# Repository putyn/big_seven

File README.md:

big_seven
=========

3" seven segments wifi clock with a beautiful wooden case

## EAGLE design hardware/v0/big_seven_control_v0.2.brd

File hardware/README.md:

##big_seven hardware

Initital hardware was suppose to have individual current sources for every segement of the display similar to this https://www.dorkbotpdx.org/blog/paul/big_7segment_countdown_timer, until i found the TPIC6x595 which has the same functionality as the 74HC595 (shift register) only higher output voltage.

For the brains the ESP8266 was chosen, simply because its cheap its supporeted by the Arduino IDE and has WiFi. 

##leasens to learn
1. never again use LDO to drop high voltage to low voltage @ high currents https://github.com/esp8266/Arduino/issues/1840

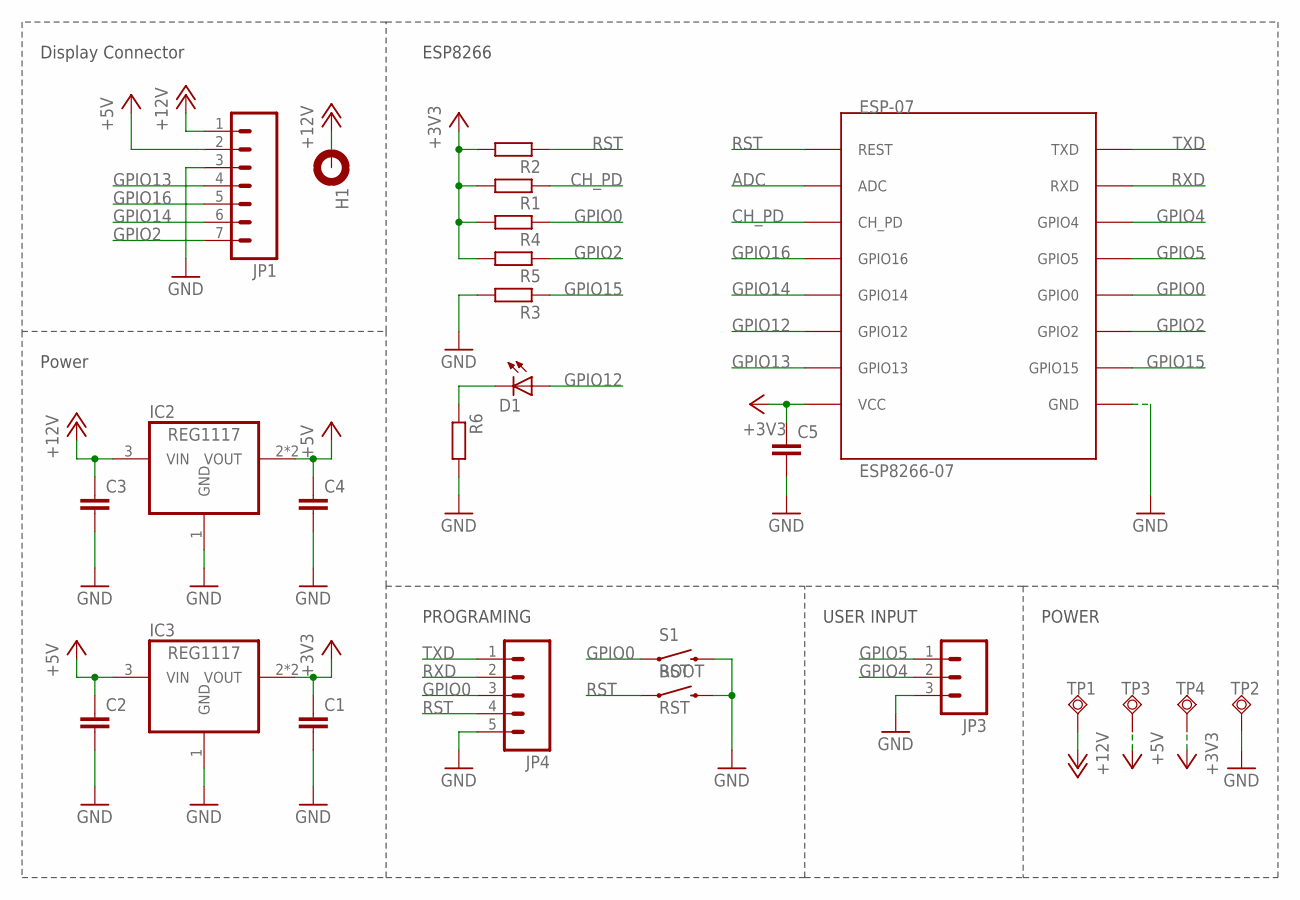
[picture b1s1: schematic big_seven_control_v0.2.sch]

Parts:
C1, C2, C3, C4: C-EUC1206K; C1206K
C5: C-EUC0805; C0805
D1: LEDCHIP-LED0805; CHIP-LED0805
ESP-07: ESP8266-07; ESP-07
H1: MOUNT-PAD-ROUND3.2; 3,2-PAD
IC2, IC3: REG1117; SOT223
JP1: M07LOCK; 1X07_LOCK
JP3: M03LOCK; 1X03_LOCK
JP4: M05LOCK; 1X05_LOCK
R1, R2, R3, R4, R5, R6: R-EU_R0805; R0805
RST: RST; TACTILE-SWITCH-SMD
S1: BOOT; TACTILE-SWITCH-SMD
TP1: 12V; TP20R
TP2: delk; TP20R
TP3: 5V; TP20R
TP4: 3V3; TP20R

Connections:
+3V3: C1.1, C5.1, ESP-07.VCC, IC3.2 (VOUT), IC3.4 (VOUT), R1.2, R2.2, R4.2, R5.2, TP4.TP
+5V: C2.1, C4.1, IC2.2 (VOUT), IC2.4 (VOUT), IC3.3 (VIN), JP1.2, TP3.TP
+12V: C3.1, H1.B3,2, IC2.3 (VIN), JP1.1, TP1.TP
ADC: ESP-07.ADC
CH_PD: ESP-07.CH_PD, R1.1
GND: C1.2, C2.2, C3.2, C4.2, C5.2, ESP-07.GND, IC2.1 (GND), IC3.1 (GND), JP1.3, JP3.3, JP4.5, R3.2, R6.2, RST.3 (2), S1.3 (2), TP2.TP
GPIO0: ESP-07.GPIO0, JP4.3, R4.1, S1.1
GPIO2: ESP-07.GPIO2, JP1.7, R5.1
GPIO4: ESP-07.GPIO4, JP3.2
GPIO5: ESP-07.GPIO5, JP3.1
GPIO12: D1.A, ESP-07.GPIO12
GPIO13: ESP-07.GPIO13, JP1.4
GPIO14: ESP-07.GPIO14, JP1.5
GPIO15: ESP-07.GPIO15, R3.1
GPIO16: ESP-07.GPIO16, JP1.6
unnamed: D1.C, R6.1
RST: ESP-07.REST, JP4.4, R2.1, RST.1
RXD: ESP-07.RXD, JP4.2
TXD: ESP-07.TXD, JP4.1

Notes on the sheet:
Display Connector
Power
ESP8266
PROGRAMING
USER INPUT
POWER

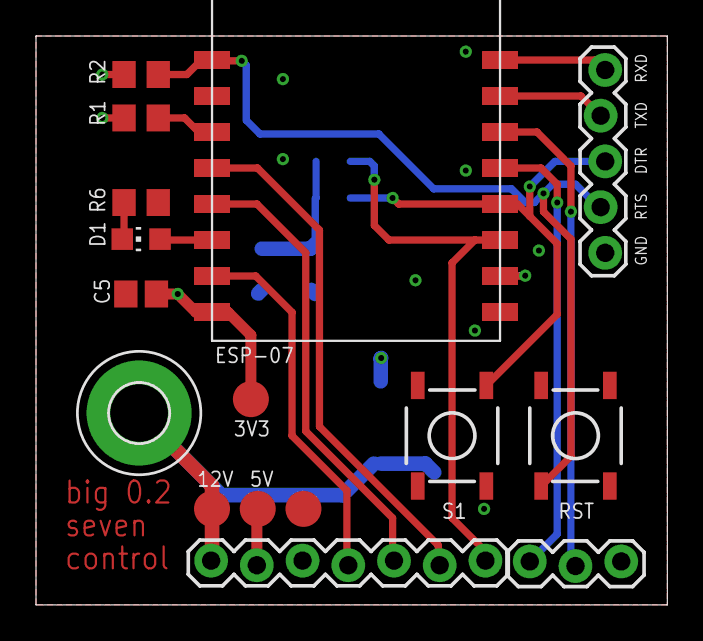
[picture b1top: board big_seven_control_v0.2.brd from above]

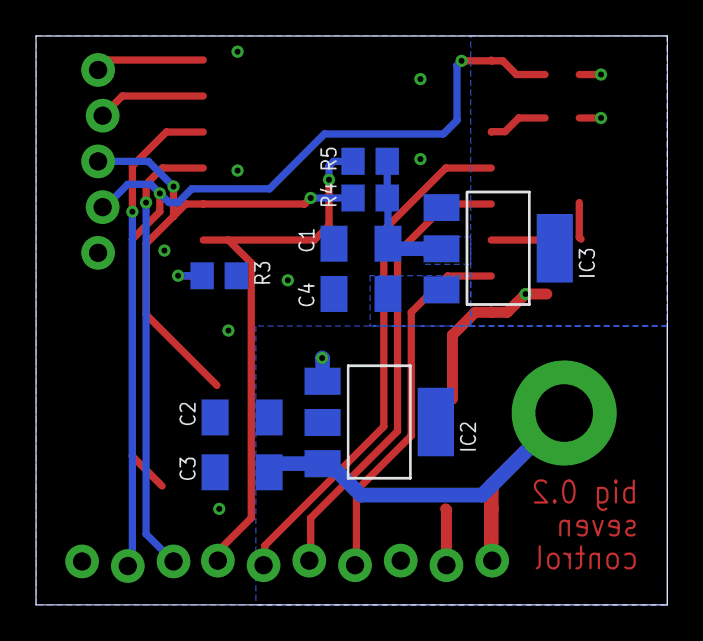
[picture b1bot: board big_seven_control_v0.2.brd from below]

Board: 2 copper layers, 35.1 x 31.6 mm, 25 parts (9 on the bottom side), 18 nets.

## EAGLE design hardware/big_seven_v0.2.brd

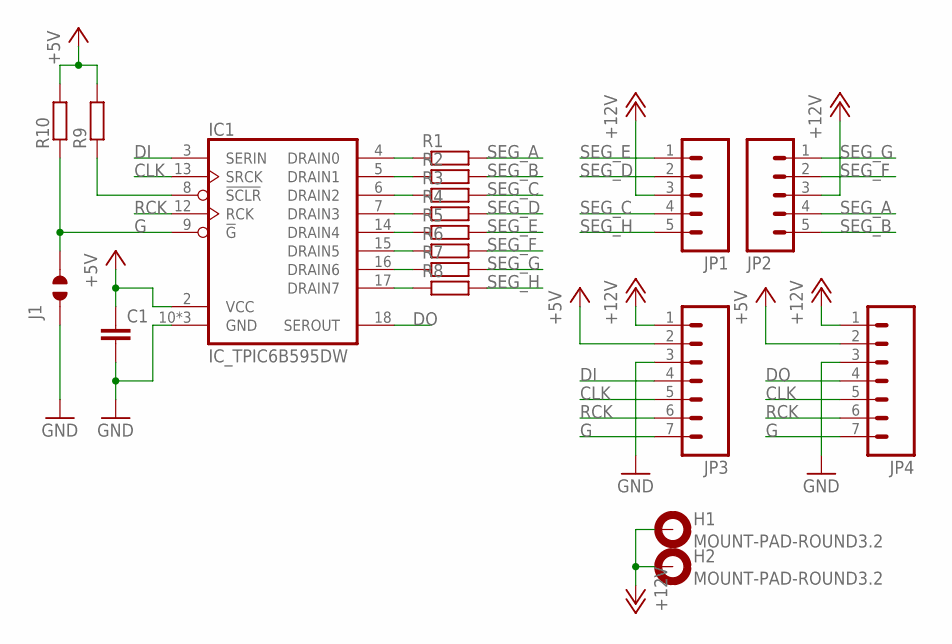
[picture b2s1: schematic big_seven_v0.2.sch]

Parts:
C1: C-EUC0805; C0805
H1, H2: MOUNT-PAD-ROUND3.2; 3,2-PAD
IC1: IC_TPIC6B595DW; SOIC-20
J1: JUMPER_SOLDER_1X2
JP1, JP2: M05PTH; 1X05
JP3, JP4: M07LONGPADS; 1X07_LONGPADS
R1, R2, R3, R4, R5, R6, R7, R8: R-EU_M1206; M1206
R9, R10: R-EU_M0805; M0805

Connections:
+5V: C1.1, IC1.2 (VCC), JP3.2, JP4.2, R9.2, R10.2
+12V: H1.B3,2, H2.B3,2, JP1.3, JP2.3, JP3.1, JP4.1
CLK: IC1.13 (SRCK), JP3.5, JP4.5
DI: IC1.3 (SERIN), JP3.4
DO: IC1.18 (SEROUT), JP4.4
G: IC1.9 (!G), J1.2, JP3.7, JP4.7, R10.1
GND: C1.2, IC1.10 (GND), IC1.11 (GND), IC1.19 (GND), J1.1, JP3.3, JP4.3
unnamed: IC1.4 (DRAIN0), R1.1
unnamed: IC1.5 (DRAIN1), R2.1
unnamed: IC1.6 (DRAIN2), R3.1
unnamed: IC1.7 (DRAIN3), R4.1
unnamed: IC1.14 (DRAIN4), R5.1
unnamed: IC1.15 (DRAIN5), R6.1
unnamed: IC1.16 (DRAIN6), R7.1
unnamed: IC1.17 (DRAIN7), R8.1
unnamed: IC1.8 (!SCLR), R9.1
RCK: IC1.12 (RCK), JP3.6, JP4.6
SEG_A: JP2.4, R1.2
SEG_B: JP2.5, R2.2
SEG_C: JP1.4, R3.2
SEG_D: JP1.2, R4.2
SEG_E: JP1.1, R5.2
SEG_F: JP2.2, R6.2
SEG_G: JP2.1, R7.2
SEG_H: JP1.5, R8.2

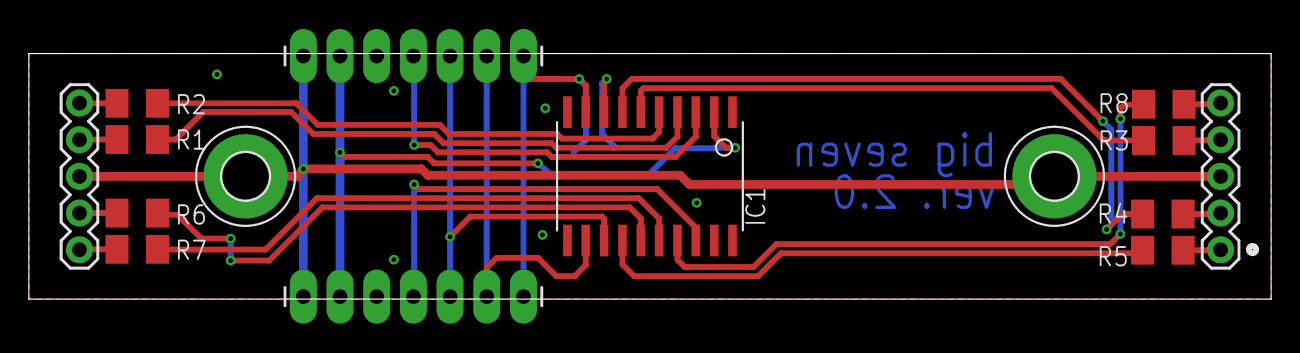
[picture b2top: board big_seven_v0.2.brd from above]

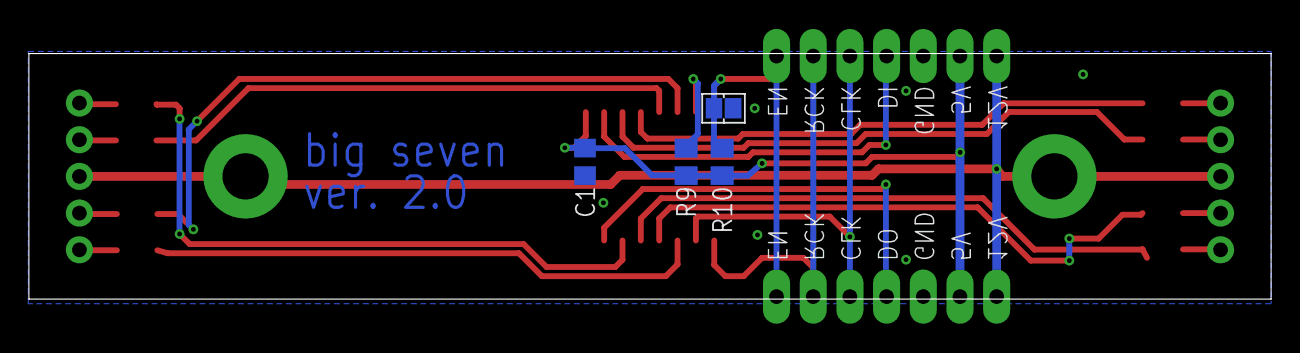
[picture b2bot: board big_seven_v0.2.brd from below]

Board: 2 copper layers, 86.0 x 17.0 mm, 19 parts (4 on the bottom side), 25 nets.

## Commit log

2017-03-04 initial commit #4
2017-03-19 first try with dashboard template from bootstrap
2017-03-21 more work on webui, added handles for /time /overview
2017-03-22 time settings save/read + code changes
2017-03-26 webui ready to be merged back to trunk
2017-03-26 webui code merged with old code
2017-04-03 clenup + webui work
    HW section added to webui for controlling various things like display brightness, firmware upgrade
2017-04-19 moved webui to new repo should be used a library

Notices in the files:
parts and their libraries:
SparkFun-Connectors: Licensing: CC v3.0 Share-Alike You are welcome to use this library for commercial purposes.
SparkFun-Electromechanical: Licensing: Creative Commons ShareAlike 4.0 International - https://creativecommons.org/licenses/by-sa/4.0
